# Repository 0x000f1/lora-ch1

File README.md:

# lora-ch1

This project is based on the ESP32-C3 microcontroller that behaves like a bridge between mobile devices and the modules. The connection is established via Bluetooth Low Energy with the phone, then sends the package over the LoRa (RFM98W/SX1278) module at 433 MHz. This combination is able to perform a full internet-independent communication between two or more devices, at a long range.

## Hardware Specification & Pinout

The current hardware is based on the ESP32-C3 microcontroller, interfaced with an RFM98W/SX1278 LoRa module, a DRV2605L haptic driver, and a BQ24075 based charging circuit.

### ESP32-C3 GPIO Mapping

| Component | Pin Name | ESP32-C3 GPIO | Description |
| :--- | :--- | :--- | :--- |
| **LoRa (SPI)** | MISO | GPIO 5 | Master In Slave Out |
| | MOSI | GPIO 6 | Master Out Slave In |
| | NSS | GPIO 7 | Chip Select (CS) |
| | SCK | GPIO 4 | SPI Clock |
| | DIO1 | GPIO 3 | IRQ / Interrupt 1 |
| | DIO0 | GPIO 10 | IRQ / Interrupt 0 |
| | RST | GPIO 2 | LoRa Reset |
| **I2C Bus** | SDA | GPIO 8 | I2C Data (DRV2605L) |
| | SCL | GPIO 9 | I2C Clock (DRV2605L) |
| **Haptic Driver** | DRV_EN | GPIO 21 | Enable pin for DRV2605L |
| **Power / Battery** | CHRG | GPIO 20 | Charging status (BQ24075, LOW = charging) |
| | BAT_SENS | GPIO 1 | Battery Voltage ADC (ADC_11db attenuation) |
| **User Input** | BUTTON | GPIO 0 | Hardware Button (with debouncing) |

### Development Environment & Flashing
* **IDE:** **PlatformIO**
* **Board:** **`esp32-c3-devkitm-1`**

## Functions

* **Reliable Bidirectional Communication:** Transmit packages seamlessly between two or more devices. Supports public Broadcasts and private P2P messages with an Automatic Repeat Request (ARQ) mechanism. P2P messages are automatically acknowledged (ACK) and retried up to 3 times if lost in the air. The system utilizes a dynamic ACK timeout mechanism, calculating the exact wait time based on the payload's Time on Air (ToA) and the mandatory 10% Duty Cycle off-time, ensuring reliable retries without regulatory violations.
* **Fast TX & Continuous RX Architecture:** Optimized for ultra-low latency and high reliability in the prototype phase. By utilizing an optimized preamble (12 symbols), the Time on Air (ToA) is reduced to ~100-132ms (payload dependent), virtually eliminating packet collisions while ensuring zero message drops through continuous background listening. *Thread-safe FreeRTOS implementation prevents conflicts between BLE and LoRa tasks*.
* **End-to-End Encryption Support (Key Exchange):** Natively supports routing public keys for E2EE via `KEY_REQ` and `KEY_RESP` commands over the standard data characteristic. The key exchange utilizes the existing ARQ (Hardware ACK) mechanism ensuring reliable and verified key delivery between peers.
* **Offline Message Buffer:** Safely stores up to 32 incoming direct (P2P) messages in the RAM if the phone is disconnected. Upon BLE reconnection, all buffered messages are instantly pushed to the app. Public Broadcasts are ignored for offline storage to preserve memory.
* **Smart Neighbour Discovery:** Automatic heartbeat messages are sent out to advertise the active device among other users, storing the RSSI, last active timestamp, and the user's custom RGB UI color. The system automatically cleans up "dead" or out-of-range nodes after a timeout period based on the active power profile.
* **Location Sharing & Privacy:** Broadcasts the user's GPS coordinates (Latitude and Longitude) to the mesh network via Heartbeat messages. If the user disables location sharing (Privacy Mode), the system dynamically truncates the binary payload by 8 bytes to conserve precious LoRa airtime and battery life.
* **Haptic & UI Feedback:** Integrated DRV2605L haptic motor driver and hardware button with debouncing. Provides distinct physical feedback for button presses, incoming LoRa messages, and an automatic low battery warning (triggered below 15% while discharging).
* **BLE Security (Just Works):** Implements physical button-press validation to activate BLE advertising (Pairing Mode) for 60 seconds, preventing unauthorized external connections.
* **Dynamic NVS Management:** The device name, UUIDs, unique LoRa ID, haptic profile, and user preferences (Username, UI Color, Location) are generated on the first startup and safely stored in the Non-Volatile Storage (NVS).
* **Duty Cycle Monitoring:** Tracks and logs the Time on Air (ToA) and calculates the current duty cycle percentage to assist with regulatory compliance (e.g., the 10% limit on 433MHz in Europe).
* **Automated Power Management:** Supports 3 different power profiles (`BATTERY_SAVER`, `BALANCED`, `PERFORMANCE`) that dynamically scale the CPU frequency (80MHz or 160MHz) and adjust heartbeat intervals (10 min, 5 min, and 1 min respectively). The device defaults to `BATTERY_SAVER` on boot. Pressing the hardware button temporarily wakes the system into `BALANCED` mode for BLE communication.
* **Real Battery Monitoring:** Built-in hardware ADC integration calculates real battery percentage, and monitors the active charging status via the BQ24075 charging IC's open-drain output (GPIO 20).

## BLE API Documentation

The mobile app connects to the ESP32 and manages the LoRa module (and some settings).

### 1. Discovering the device (Scanning & Connection)

* **IMPORTANT (MTU Size):** The Android application **MUST** request an MTU size of 512 bytes (`requestMtu(512)`) immediately after the connection is established. Without this, Android will truncate incoming messages to 20 bytes! iOS handles this automatically.
* **Device Name:** The ESP32 starts advertising in this format `lora-ch1-XXXX` where the `XXXX` is the device's MAC address's last 2 bytes (e.g., `lora-ch1-A1B2`).
* **Dynamic UUIDs:** **IMPORTANT!** On the first start, the device generates (Version 4) UUIDs for the services and characteristics. The mobile device should use **Service Discovery** instead of hardcoded UUIDs!
* **Pairing Mode:** The device is hidden by default. Press the physical button on the device to enable Bluetooth visibility for 60 seconds.

### 2. Services and characteristics

The system advertises a single main Service, under which two characteristics (Data and Control) are located. Both characteristics support `READ`, `WRITE`, and `NOTIFY` operations.

#### A. Data Characteristic
Actual message sending and receiving takes place on this channel. The payload must follow a semicolon-separated format to support message fragmentation and direct addressing.

* **Sending (App -> LoRa):**
  * **Format 1 (Standard Message):** `TARGET_MAC;CURRENT_FRAGMENT;TOTAL_FRAGMENTS;PAYLOAD`
    * Write a String to this characteristic using the format above.
    * *Target MAC:* 8-character HEX string. Use `FFFFFFFF` to Broadcast to everyone, or a specific device's LoRa ID for a private P2P message.
    * *Example (Broadcast):* `FFFFFFFF;1;1;Hello everyone!`
    * *Example (P2P Fragmented):* `ABCD1234;1;3;This is a long me`
    * *Limitation:* The `PAYLOAD` length per BLE write should be kept around 240 bytes due to LoRa airtime limitations.
  * **Format 2 (Key Exchange):** `KEY_REQ;TARGET_MAC;PUBLIC_KEY` or `KEY_RESP;TARGET_MAC;PUBLIC_KEY`
    * Initiates or responds to an End-to-End Encryption key exchange.
    * The ESP32 automatically parses the `TARGET_MAC`, forwards the key via LoRa, and awaits a hardware ACK from the target device.
    * *Example:* `KEY_REQ;A1B2C3D4;PU8r8H3BvjiyDNbqtp12Y1LHFvhF+nJI81oWjmFqS1w=`

* **Receiving (LoRa -> App):**
  * The app must subscribe to `NOTIFY` events on this characteristic.
  * **Format 1 (Standard Data):** `SENDER_MAC;SENDER_USERNAME;COLOR_HEX;TARGET_MAC;CURRENT_FRAGMENT;TOTAL_FRAGMENTS;TIMESTAMP;RSSI;PAYLOAD`
    * The app can use the `TARGET_MAC` to determine if the received message was a public broadcast (`FFFFFFFF`) or a private P2P message.
    * `SENDER_USERNAME`: The sender's username string automatically resolved from the internal neighbor cache. Returns `Unknown` if the sender is not in the cache.
    * `COLOR_HEX`: The sender's custom UI color (e.g., `FF0000`) resolved from the cache. Defaults to `0088FF` if unknown.
    * `TIMESTAMP`: The UNIX Epoch time in seconds. If the device clock is not synced via `SET_TIM`, this value returns `0`. For fragmented messages (total fragments > 1), all fragments of the same message will share the exact same timestamp (derived from the first received fragment), allowing the mobile app to seamlessly group them.
    * `RSSI`: The signal strength of the received LoRa package (e.g., `-78.00`).
  * **Format 2 (Delivery Success):** `ACK_OK;TARGET_MAC`
    * Sent to the app when a previously sent P2P message (or Key Exchange) is successfully acknowledged by the receiver's hardware.
  * **Format 3 (Delivery Failed):** `ERR_TIMEOUT;TARGET_MAC`
    * Sent to the app when a P2P message fails to reach the target after maximum retries or channel collisions.
  * **Format 4 (Key Exchange):** `KEY_REQ;SENDER_MAC;PUBLIC_KEY` or `KEY_RESP;SENDER_MAC;PUBLIC_KEY`
    * Sent to the app when another device initiates or responds to a key exchange. The app can use the `SENDER_MAC` to identify the peer and complete the encryption setup.

#### B. Control Characteristic
This channel is used to query the network status and manage system preferences.

* **Commands (App -> ESP32) & Responses (via NOTIFY):**
  * `SET_TIM;UnixSeconds`
    * *Action:* Syncs the ESP32's internal RTC to the real-world UNIX epoch time (e.g., `SET_TIM;1715423000`). Must be sent immediately after connecting.
    * *Response:* `TIM_OK`
  * `SET_LOC;Latitude;Longitude`
    * *Action:* Updates the device's internal location cache with the phone's GPS coordinates to be broadcasted via LoRa (e.g., `SET_LOC;47.5316;21.6273`).
    * *Response:* `LOC_OK` or `LOC_ERR`
  * `GET_LOC`
    * *Response:* `LOC;Latitude;Longitude` (e.g., `LOC;47.531600;21.627300`).
  * `NO_LOC`
    * *Action:* Disables location sharing for privacy. Resets the coordinates to `0.0` and dynamically truncates the LoRa heartbeat payload to save bandwidth.
    * *Response:* `NO_LOC_OK`
  * `GET_NEI`
    * *Response:* `NEI|MAC;NEI_USERNAME;COLOR_HEX;RSSI;TIMESTAMP;LATITUDE;LONGITUDE|...` (e.g., `NEI|A1B2C3D4;lora-ch1-XXXX;FF0000;-45.50;32125;47.531600;21.627300|...`) or `NEI|NO_NEI` if the list is empty.
  * `GET_BAT`
    * *Response:* `BAT;Percentage;IsCharging` (e.g., `BAT;87;1` where 1 means charging, 0 means discharging).
  * `SET_USR;Username`
    * *Action:* Saves the string to NVS. Cannot contain `;` or `|` characters, and trims whitespaces. Defaults to `Guest` if empty or invalid.
    * *Response:* `USR_OK`
  * `GET_USR`
    * *Response:* `USR;Username` (Defaults to `Guest` if not set).
  * `SET_COL;HexColor`
    * *Action:* Saves the UI color HEX string to NVS (e.g., `FF0000`). Reverts to `0088FF` if the format is invalid.
    * *Response:* `COL_OK`
  * `GET_COL`
    * *Response:* `COL;HexColor` (Defaults to `0088FF` if not set).
  * `SET_PWR;ProfileName`
    * *Action:* Sets the active power profile (`BATTERY_SAVER`, `BALANCED`, `PERFORMANCE`).
    * *Response:* `PWR_OK` or `PWR_ERR` (if the profile name is invalid).
  * `GET_VIB`
    * *Response:* `VIB;{0/1}` Where 0 means haptics is off, 1 means haptics is on.
  * `SET_VIB;STATUS`
    * *Action:* `1` turns on (by default) the haptic feedback actuator, `0` turns off.
    * *Response:* `VIB_OK` means the command ran.
  * `GET_ID`
    * *Response:* `ID;LOCAL_ID` (e.g., `ID;3FFE78C0`) returns the LoRa local address.
  * `RST`
    * *Action:* Restarts the ESP, needs to reconnect after!
    * *Response:* `RST_OK`
  * `FACTORY_RESET`
    * *Action:* Erases the whole NVS partition, clears color, username, UUIDs, and all settings. The ESP restarts automatically. The LoRa MAC remains unchanged as it is generated from the hardware MAC address.
    * *Response:* `FACTORY_RESET_OK`
  * `FIND`
    * *Action:* For 5 second, spams the 750 ms Alert 100% haptic vibration.
    * *Response:* `FIND_OK`

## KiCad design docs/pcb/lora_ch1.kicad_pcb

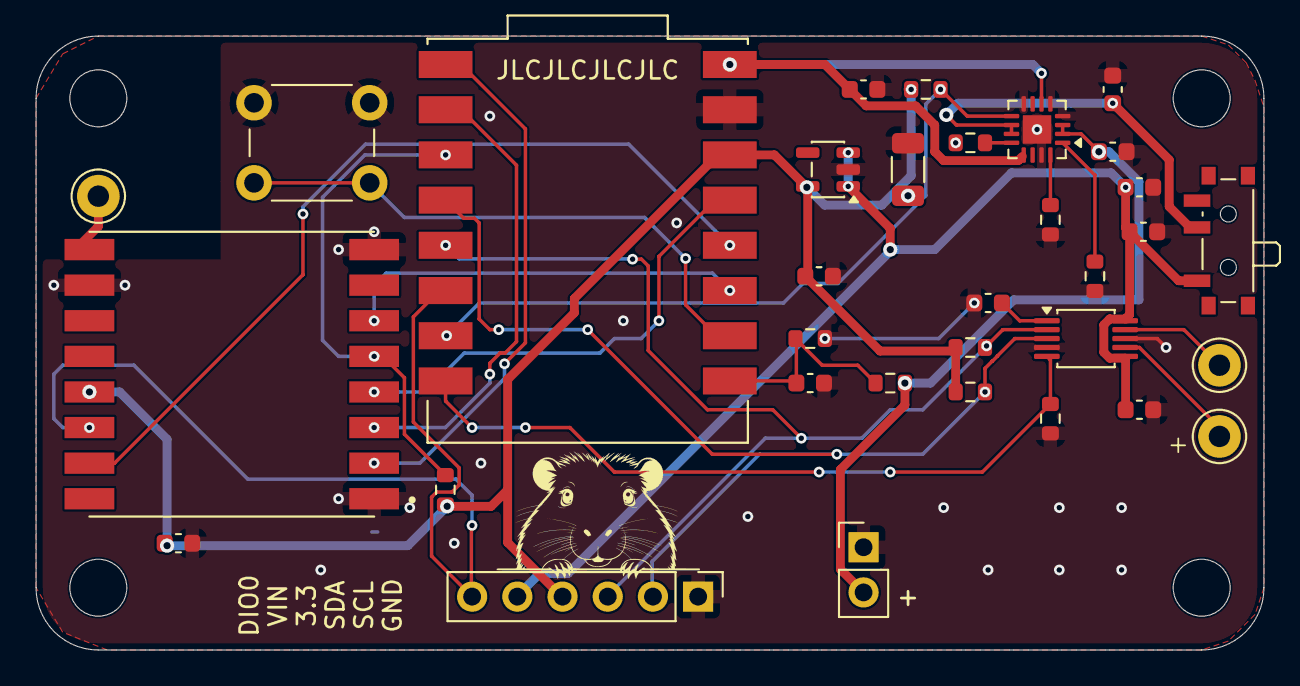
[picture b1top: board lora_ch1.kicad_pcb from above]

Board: 2 copper layers, 69.0 x 34.5 mm, 37 parts (0 on the bottom side), 26 nets.

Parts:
+: Conn_01x02_Pin; PinHeader_1x02_P2.54mm_Vertical
ANT1: PINHD_1x1_Male; Pin_D1.0mm_L10.0mm_LooseFit
C1, C2, C5: 10uF; C_0603_1608Metric
C6: 100uF; C_1206_3216Metric
C7, C10, C11: 0.1uF; C_0603_1608Metric
C8: 1.0uF; C_0603_1608Metric
C12, C13, C14: 4.7uF; C_0603_1608Metric
CHRG1: BQ24075RGT; VQFN-16-1EP_3x3mm_P0.5mm_EP1.6x1.6mm
ESP1: ESP32-C3_SUPERMINI_SMD; MODULE_ESP32-C3_SUPERMINI
HAPTIC1: DRV2605LDGS; VSSOP-10_3x3mm_P0.5mm
INPT_BTN1: Push_Button; SW_PUSH_6mm
LDO1: XC6220B331MR; SOT-23-5
LORA1: RFM98W-433S2; XCVR_RFM98W-433S2
LRAM1: PINHD_1x1_Male; Pin_D1.0mm_L10.0mm_LooseFit
LRAP1: PINHD_1x1_Male; Pin_D1.0mm_L10.0mm_LooseFit
MOUNT1, MOUNT2, MOUNT3, MOUNT4: MountingHole_M3; MountingHole_3.2mm_M3
R2: 5.1k; R_0603_1608Metric
R3, R8, R11: 100k; R_0603_1608Metric
R4, R5: 4.7k; R_0603_1608Metric
R9, R10: 1.8k; R_0603_1608Metric
R12, R13: 12k; R_0603_1608Metric
SW1: SW_SPDT; SW_SPDT_PCM12
TEST1: PINHD_1x6_Male; PinHeader_1x06_P2.54mm_Vertical

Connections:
3.3V: C1.2, C6.2, C7.1, ESP1.3.3 (3V3), LDO1.5 (VOUT), LORA1.13 (3.3V), R2.1, R4.2, R5.1, R12.1, TEST1.4
ANT: ANT1.1, LORA1.9 (ANT)
BATT_PLUS: +.2, C13.1, CHRG1.2 (BAT), CHRG1.3 (BAT), R8.2
CHRG: CHRG1.9 (~CHG), ESP1.20 (GPIO20), R12.2
DRV_EN: ESP1.21 (GPIO21), HAPTIC1.5 (EN), R11.2
GND: +.1, C1.1, C2.1, C5.1, C6.1, C7.2, C8.2, C10.1, C11.2, C12.2, C13.2, C14.2, CHRG1.4 (~CE), CHRG1.5 (EN2), CHRG1.8 (VSS), CHRG1.15 (SYSOFF), CHRG1.17 (VSS), ESP1.G (GND), HAPTIC1.4 (IN/TRIG), HAPTIC1.8 (GND), INPT_BTN1.1, LDO1.2 (GND), LORA1.1 (GND), LORA1.8 (GND), LORA1.10 (GND), R3.2, R9.2, R10.1, R11.1, R13.1, TEST1.1
LORA_DIO0: ESP1.10 (GPIO10), LORA1.14 (DIO0), TEST1.6
LORA_DIO1: ESP1.3 (GPIO3), LORA1.15 (DIO1)
LORA_MISO: ESP1.5 (GPIO5), LORA1.2 (MISO)
LORA_MOSI: ESP1.6 (GPIO6), LORA1.3 (MOSI)
LORA_NSS: ESP1.7 (GPIO7), LORA1.5 (NSS), R2.2
LORA_RST: ESP1.2 (GPIO2), LORA1.6 (RESET)
LORA_SCK: ESP1.4 (GPIO4), LORA1.4 (SCK)
LRA+: HAPTIC1.7 (OUT+), LRAP1.1
LRA-: HAPTIC1.9 (OUT-), LRAM1.1
unnamed: CHRG1.12 (ILIM), R10.2
unnamed: CHRG1.16 (ISET), R9.1
unnamed: CHRG1.1 (TS), R13.2
unnamed: C10.2, ESP1.0 (GPIO0), R3.1, R8.1
unnamed: ESP1.1 (GPIO1), INPT_BTN1.2
unnamed: C8.1, HAPTIC1.1 (REG)
SCL: ESP1.9 (GPIO9), HAPTIC1.2 (SCL), R5.2, TEST1.3
SDA: ESP1.8 (GPIO8), HAPTIC1.3 (SDA), R4.1, TEST1.2
SYS_PWR: C14.1, CHRG1.10 (OUT), CHRG1.11 (OUT), SW1.2 (B)
V_IN: C2.2, C5.2, C11.1, HAPTIC1.6 (VDD/NC), HAPTIC1.10 (VDD), LDO1.1 (VIN), LDO1.3 (CE), SW1.1 (A), TEST1.5
V_USB: C12.1, CHRG1.6 (EN1), CHRG1.13 (IN), ESP1.5V

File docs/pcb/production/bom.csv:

Designator,Footprint,Quantity,Value,LCSC Part #
"C1, C2, C5",0603,3,10uF,C19702
"C10, C11, C7",0603,3,0.1uF,C14663
"C12, C13, C14",0603,3,4.7uF,C19666
C6,1206,1,100uF,C15008
C8,0603,1,1.0uF,C15849
CHRG1,VQFN-16-1EP_3x3mm_P0.5mm_EP1.6x1.6mm,1,BQ24075RGT,C15464
HAPTIC1,VSSOP-10_3x3mm_P0.5mm,1,DRV2605LDGS,C527464
LDO1,SOT-23-5,1,XC6220B331MR,C22466451
"R10, R9",0603,2,1.8k,C4177
"R11, R3, R8",0603,3,100k,C25803
"R12, R13",0603,2,12k,C22790
R2,0603,1,5.1k,C23186
"R4, R5",0603,2,4.7k,C23162

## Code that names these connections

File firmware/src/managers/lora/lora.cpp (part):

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#define PREAMBLE_LENGTH 12 // SF9, BW125 -> 1 symbol: 4.096ms, 12 symbol ~ 49.15ms)
#define GAIN 0

#define LORA_SCK  4
#define LORA_MISO 5
#define LORA_MOSI 6
#define LORA_NSS  7
#define LORA_RST  2
#define LORA_DIO0 10
#define LORA_DIO1 3

// Static variables (Heartbeat, sequence number, duty cycle stats, neighbors)
TaskHandle_t LoRaManager::mainTaskHandle = NULL;
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
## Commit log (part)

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2026-02-05 Default directories, frame of the whole project.
2026-02-05 Deafult directories added.
2026-02-06 BLE basic functions, advertising and simple write functions.
2026-02-07 Simple pushMessage function added, that pushes a notification to the phone. (It triggers on message received)
2026-02-08 Log helper function, NVS storage (generator, loader) for UUID and Name added.
2026-02-08 Added comments to ble.cpp and system_manager.h. Completed basic LoRa receive/transmit functions, and connected it with the BLEManager.
2026-02-10 Flutter init
2026-02-10 PCB design files added.
2026-02-11 PCB schematic update, charging function added.
2026-02-12 LORA Pin update to keep boot sequence stable.
2026-02-12 PCB schematic finished.
2026-02-17 PCB design finished.
2026-02-18 PCB ready to print.
2026-02-22 Haptic driver setup begin (DRV2605L)
2026-02-25 Structure improvements + protocol.h for addressing and packageTypes.
2026-02-25 LoRa package header initialization + Message Types, code improvements.
2026-02-26 Power profiles added (BATTERY_SAVER, BALANCED, PERFORMANCE)
2026-02-26 Heartbeat (Device discovery function added) with variable advertising rate.
2026-02-26 Neighbor discovery function with RSSI and Timestamp structure.
2026-02-26 New characteristic for CONTROL via BLE write function.
2026-02-26 Memory management improvement (Static callbacks)
2026-02-26 Hotfix for memory management commit (code order error) in ble.cpp
2026-02-27 README update
2026-03-01 Fragmentation, addressing added and README updated with the message send API usage.
2026-03-01 Auto delete zombie neighbor, and writes out the last active timestamp to the characteristic.
2026-03-02 Direct addressing resolved, and the neighbor removing loop moved to execute with heartbeat send function.
2026-03-04 Haptic feedback initialization, and play an effect on message received.
2026-03-04 Button press function added. (Currently just handles it and plays a haptic effect.)
2026-03-04 ACK message response on P2P message received. TODO: Sender side implementation to ACK/RESEND
2026-03-04 ACK Retry / OK. On BLE the code writes characteristic notify to ACK_OK / ERR_TIMEOUT
2026-03-04 README updates
2026-03-06 Implement secure BLE Pairing Mode (Just Works) with hardware button
2026-03-06 LoRa CAD (Listen Before Talk) implementation, and resolved -24 TX error.
2026-03-07 CAD hotfix, thread-safe queued message send function called on BLE characteristic write. README update.
2026-03-13 Battery management functions added, can be changed on control characteristics with "SET_PWR;<PROFILE>" string.
2026-03-13 Resolve LoRa CAD blocking issue and implement async TX/RX
2026-03-16 BLE completely turned off while disconnected, stops advertising and 'sleeps' at ~20mA
2026-03-20 Basic UI with bottom navigation bar
2026-03-20 bt_sheet and theme files added
2026-03-20 Basic UI fix
2026-03-20 Bottom bar theme updated + font added
2026-04-16 CAD function ignored on SX1278, listening always without CAD implemented.
2026-04-16 Revert "CAD function ignored on SX1278, listening always without CAD implemented."
    This reverts commit 7ddfc94e589f47eaf240261d2b1e9211bfd936e6.
2026-04-17 Reapply "CAD function ignored on SX1278, listening always without CAD implemented."
    This reverts commit ba692f1b1611bafccdbb9f819575b8c408437e7b.
2026-04-17 refactor: removed CAD for Fast TX architecture, expanded BLE API (NVS user config) & fixed DIO0 interrupt bug
2026-04-19 NVS Caching added, BLE pairing function improved, String usage reduced in system_manager
2026-04-19 Broadcast message can be sent
2026-04-20 Comment fix, .step sample added for printing + consumption table generated (without energy management)
2026-06-19 PCB rework, added DIO1 connection to GPIO3, changed DIO0 location to GPIO2. Changed the charging controller from TP4056 to BQ24075RGT.
